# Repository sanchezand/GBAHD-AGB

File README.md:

# GBAHD-AGB Motherboard
This is a replacement AGB motherboard shield for the [gbaHD project](https://github.com/zwenergy/gbaHD).  
- The aim is to remove the CPU and RAM from an original AGB motherboard and place them in this new board.  
- Uses an MCU to connect a classic controller.  
- Has a cartridge slot with a switch to detect DMG/CGB games and switch voltages.
- Has a power switch circuitry to replace Spartan Edge switch.
- Has a better footprint for 3D printed cases

## Issues
- NOT TESTED YET
- Cart sensor switch might need to be changed
- Cart sensor switch footprint might be wrong.
- Clock might need to be rerouted.
- Link port might need to be rerouted
- No 3D printed case (yet)

## Contributing
I am **NOT** an electrical engineer. Take this as a hobby project from a software engineer's attempt at something cool. If you wish to contribute, see something wrong or want to add a feature please make a pull request or leave an issue!

## BOM
Add this later...

## Programming the MCU
**FIRMWARE NOT YET WRITTEN** (following instructions still work)

In order to program the MCU, you need an arduino to use as ISP.  
Use the following image to wire up an arduino to the board to program it.  
**I would also recomend not programming it while seated in the FPGA board.**
  
After wiring the board, follow this tutorial to flash the bootloader and the sketch to the board.  
[ICSP Tutorial](https://www.arduino.cc/en/pmwiki.php?n=Tutorial/ArduinoISP)  
  
The Arduino code requires the [NintendoExtensionCtrl](https://github.com/dmadison/NintendoExtensionCtrl) library.

## Credits
This project would've not existed if it werent for people with real electrical engineering knowledge!
- ARCADETV - (Their AGB schematics seem to have dissapeared)
- Derek F - [GBA-2 Go](https://hackaday.io/project/169998-gba-2-go)
- Zwenergy - [GBAHD Creator](https://github.com/zwenergy/gbaHD)
- dmadison - [Nintendo Controller Libraries](https://github.com/dmadison/NintendoExtensionCtrl)

## Images

## LICENSE
This documentation describes Open Hardware and is licensed under the CERN OHL v. 1.2.
You may redistribute and modify this documentation under the terms of the CERN OHL v.1.2. (http://ohwr.org/cernohl). This documentation is distributed WITHOUT ANY EXPRESS OR IMPLIED WARRANTY, INCLUDING OF MERCHANTABILITY, SATISFACTORY QUALITY AND FITNESS FOR A PARTICULAR PURPOSE. Please see the CERN OHL v.1.2 for applicable conditions.

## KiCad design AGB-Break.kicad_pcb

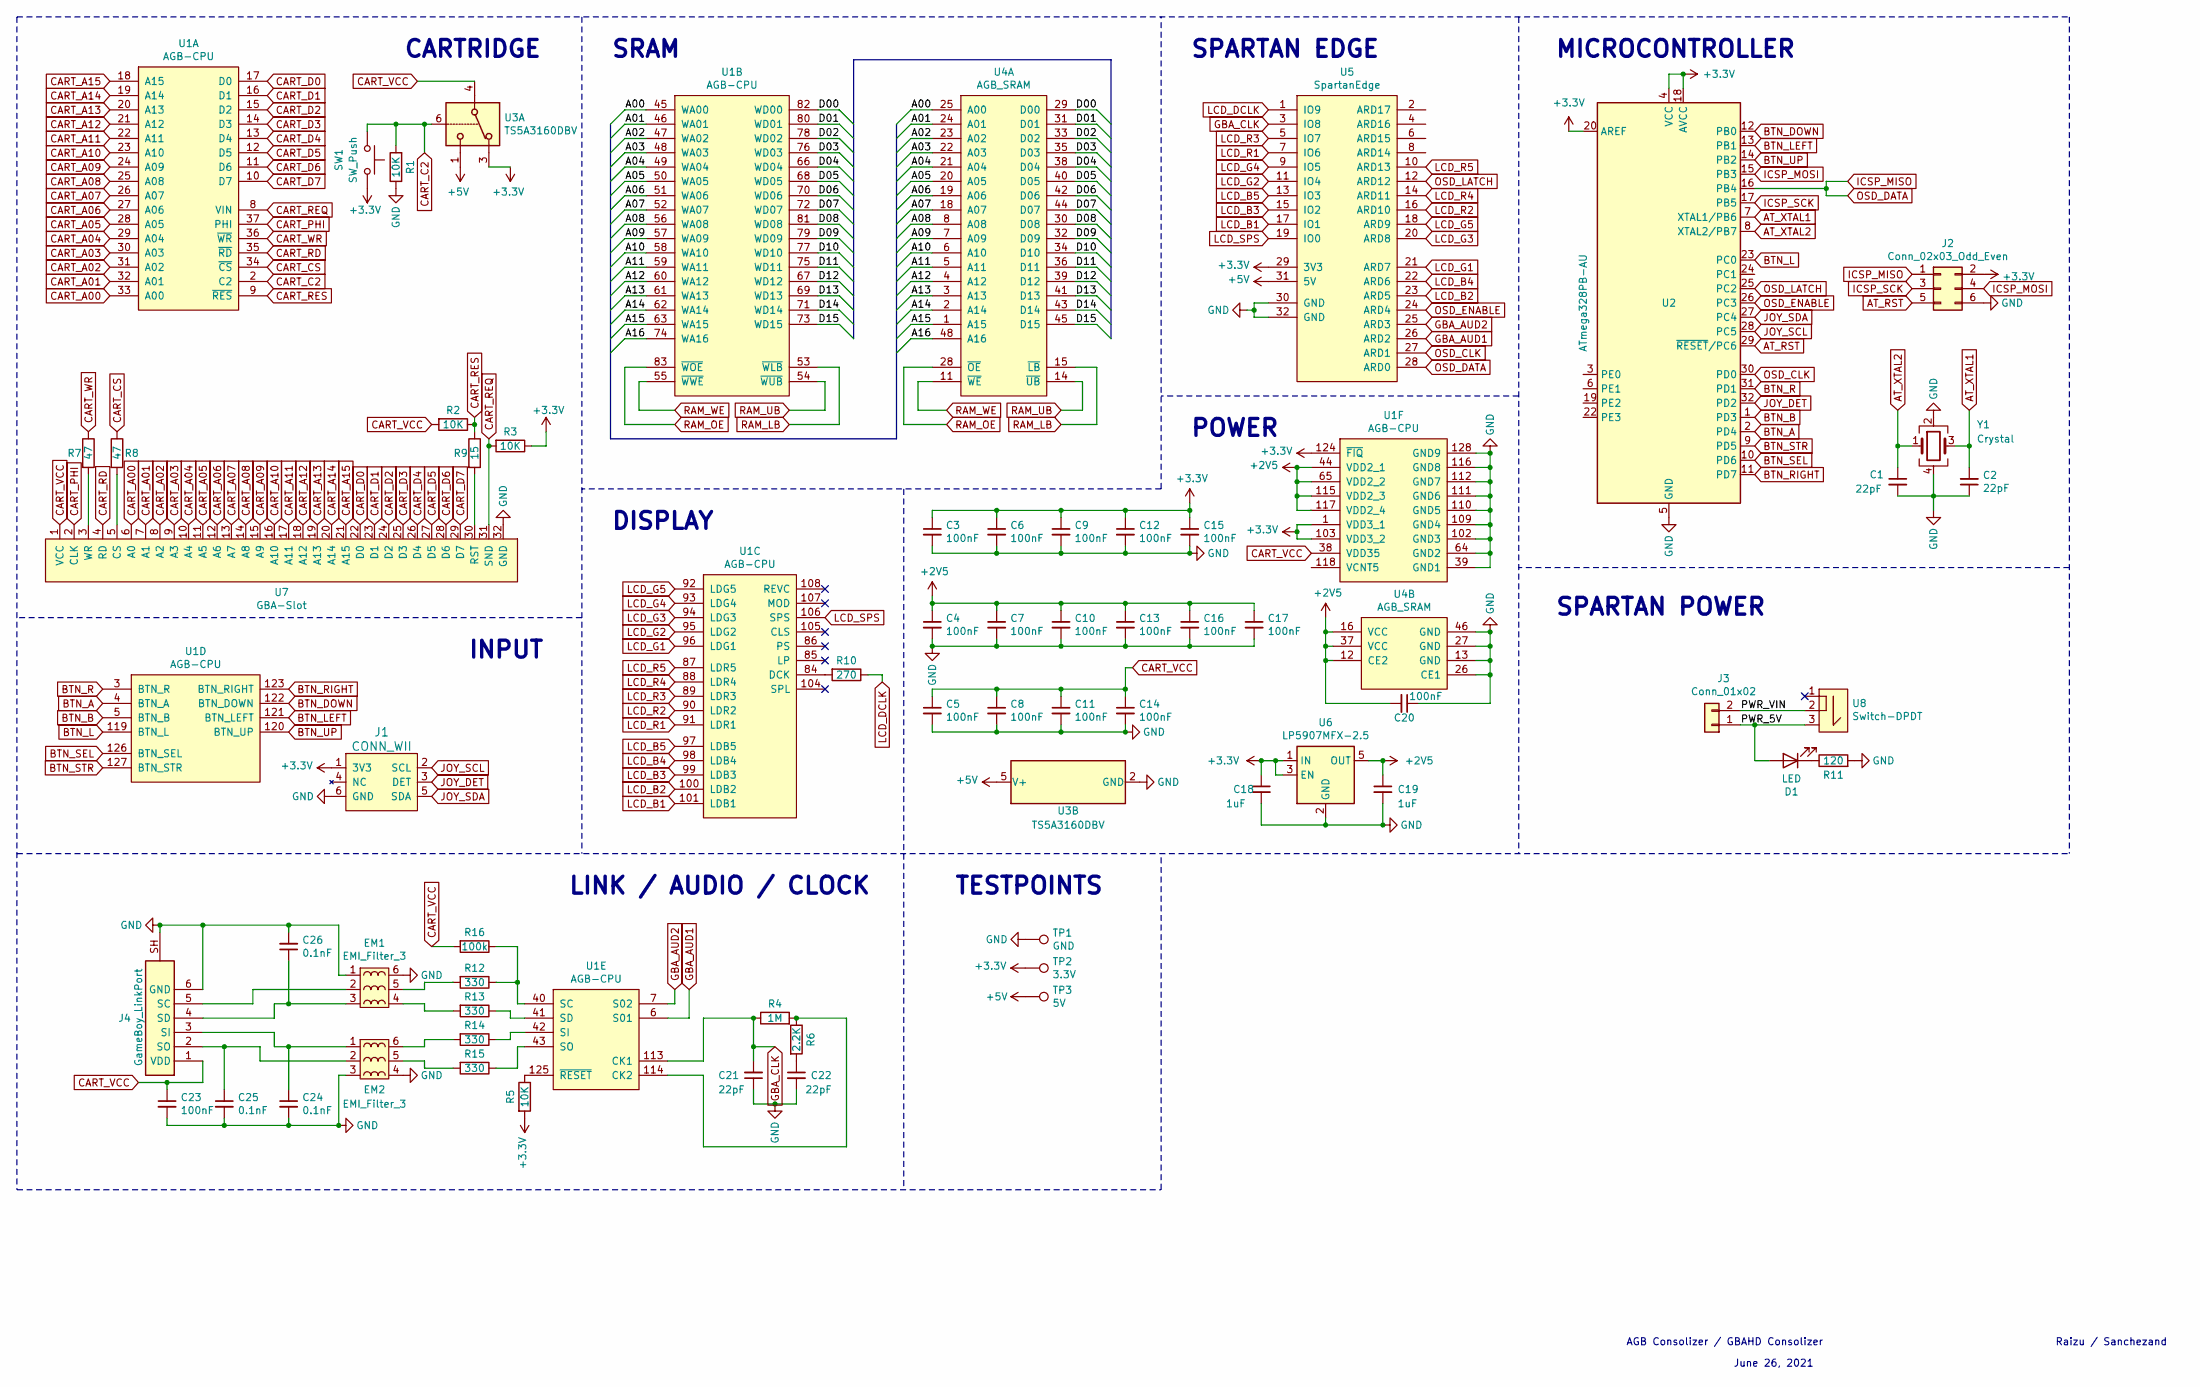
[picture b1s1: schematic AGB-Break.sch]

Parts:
C1, C2, C21, C22: 22pF; C_0805_2012Metric_Pad1.18x1.45mm_HandSolder
C3, C4, C5, C6, C7, C8, C9, C10, C11, C12, C13, C14, C15, C16, C17, C20, C23: 100nF; C_0805_2012Metric_Pad1.18x1.45mm_HandSolder
C18, C19: 1uF; C_0805_2012Metric_Pad1.18x1.45mm_HandSolder
C24, C25, C26: 0.1nF; C_0805_2012Metric_Pad1.18x1.45mm_HandSolder
D1: LED; LED_D5.0mm_FlatTop
EM1, EM2: EMI_Filter_3; Inductor-1008-3P
J1: CONN_WII
J2: Conn_02x03_Odd_Even; PinHeader_2x03_P2.54mm_Vertical
J3: Conn_01x02; PinSocket_1x02_P2.54mm_Vertical
J4: GameBoy_LinkPort; GameBoy_LinkPort_MGB_Horizontal
R1, R2, R3, R5: 10K; R_0805_2012Metric_Pad1.20x1.40mm_HandSolder
R4: 1M; R_0805_2012Metric_Pad1.20x1.40mm_HandSolder
R6: 2.2K; R_0805_2012Metric_Pad1.20x1.40mm_HandSolder
R7, R8: 47; R_0805_2012Metric_Pad1.20x1.40mm_HandSolder
R9: 15; R_0805_2012Metric_Pad1.20x1.40mm_HandSolder
R10: 270; R_0805_2012Metric_Pad1.20x1.40mm_HandSolder
R11: 120; R_0805_2012Metric_Pad1.20x1.40mm_HandSolder
R12, R13, R14, R15: 330; R_0805_2012Metric_Pad1.20x1.40mm_HandSolder
R16: 100k; R_0805_2012Metric_Pad1.20x1.40mm_HandSolder
SW1: SW_Push; Switch_K5-1617SA-01
TP1: GND; SOLDER_PAD
TP2: 3.3V; SOLDER_PAD
TP3: 5V; SOLDER_PAD
U1: AGB-CPU
U2: ATmega328PB-AU; TQFP-32_7x7mm_P0.8mm
U3: TS5A3160DBV; SOT-23-6
U4: AGB_SRAM
U5: SpartanEdge; SpartanEdge_Shield
U6: LP5907MFX-2.5; SOT-23-5
U7: GBA-Slot; GBA_CONNECTOR
U8: Switch-DPDT; XKB_XKB5858-Z-C
Y1: Crystal; Crystal_SMD_3225-4Pin_3.2x2.5mm

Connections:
+2V5: C4.1, C7.1, C10.1, C13.1, C16.1, C17.1, C19.1, C20.2, U1.44 (VDD2_1), U1.65 (VDD2_2), U1.115 (VDD2_3), U1.117 (VDD2_4), U4.12 (CE2), U4.16 (VCC), U4.37 (VCC), U6.5 (OUT)
+3V3: C3.1, C6.1, C9.1, C12.1, C15.1, C18.1, J1.1 (3V3), J2.2, R3.1, R5.2, SW1.2, TP2.1, U1.1 (VDD3_1), U1.103 (VDD3_2), U1.124 (~FIQ), U2.4 (VCC), U2.18 (AVCC), U2.20 (AREF), U3.3, U5.29 (3V3), U6.1 (IN), U6.3 (EN)
+5V: TP3.1, U3.1, U3.5 (V+), U5.31 (5V)
/A00: U1.45 (WA00), U4.25 (A00)
/A01: U1.46 (WA01), U4.24 (A01)
/A02: U1.47 (WA02), U4.23 (A02)
/A03: U1.48 (WA03), U4.22 (A03)
/A04: U1.49 (WA04), U4.21 (A04)
/A05: U1.50 (WA05), U4.20 (A05)
/A06: U1.51 (WA06), U4.19 (A06)
/A07: U1.52 (WA07), U4.18 (A07)
/A08: U1.56 (WA08), U4.8 (A08)
/A09: U1.57 (WA09), U4.7 (A09)
/A10: U1.58 (WA10), U4.6 (A10)
/A11: U1.59 (WA11), U4.5 (A11)
/A12: U1.60 (WA12), U4.4 (A12)
/A13: U1.61 (WA13), U4.3 (A13)
/A14: U1.62 (WA14), U4.2 (A14)
/A15: U1.63 (WA15), U4.1 (A15)
/A16: U1.74 (WA16), U4.48 (A16)
/D00: U1.82 (WD00), U4.29 (D00)
/D01: U1.80 (WD01), U4.31 (D01)
/D02: U1.78 (WD02), U4.33 (D02)
/D03: U1.76 (WD03), U4.35 (D03)
/D04: U1.66 (WD04), U4.38 (D04)
/D05: U1.68 (WD05), U4.40 (D05)
/D06: U1.70 (WD06), U4.42 (D06)
/D07: U1.72 (WD07), U4.44 (D07)
/D08: U1.81 (WD08), U4.30 (D08)
/D09: U1.79 (WD09), U4.32 (D09)
/D10: U1.77 (WD10), U4.34 (D10)
/D11: U1.75 (WD11), U4.36 (D11)
/D12: U1.67 (WD12), U4.39 (D12)
/D13: U1.69 (WD13), U4.41 (D13)
/D14: U1.71 (WD14), U4.43 (D14)
/D15: U1.73 (WD15), U4.45 (D15)
/PWR_5V: D1.2 (A), J3.1, U8.3
/PWR_VIN: J3.2, U8.2
AT_RST: J2.5, U2.29 (~RESET~/PC6)
AT_XTAL1: C2.2, U2.7 (XTAL1/PB6), Y1.3
AT_XTAL2: C1.1, U2.8 (XTAL2/PB7), Y1.1
BTN_A: U1.4 (BTN_A), U2.2 (PD4)
BTN_B: U1.5 (BTN_B), U2.1 (PD3)
BTN_DOWN: U1.122 (BTN_DOWN), U2.12 (PB0)
BTN_L: U1.119 (BTN_L), U2.23 (PC0)
BTN_LEFT: U1.121 (BTN_LEFT), U2.13 (PB1)
BTN_R: U1.3 (BTN_R), U2.31 (PD1)
BTN_RIGHT: U1.123 (BTN_RIGHT), U2.11 (PD7)
BTN_SEL: U1.126 (BTN_SEL), U2.10 (PD6)
BTN_STR: U1.127 (BTN_STR), U2.9 (PD5)
BTN_UP: U1.120 (BTN_UP), U2.14 (PB2)
CART_A00: U1.33 (A00), U7.6 (A0)
CART_A01: U1.32 (A01), U7.7 (A1)
CART_A02: U1.31 (A02), U7.8 (A2)
CART_A03: U1.30 (A03), U7.9 (A3)
CART_A04: U1.29 (A04), U7.10 (A4)
CART_A05: U1.28 (A05), U7.11 (A5)
CART_A06: U1.27 (A06), U7.12 (A6)
CART_A07: U1.26 (A07), U7.13 (A7)
CART_A08: U1.25 (A08), U7.14 (A8)
CART_A09: U1.24 (A09), U7.15 (A9)
CART_A10: U1.23 (A10), U7.16 (A10)
CART_A11: U1.22 (A11), U7.17 (A11)
CART_A12: U1.21 (A12), U7.18 (A12)
CART_A13: U1.20 (A13), U7.19 (A13)
CART_A14: U1.19 (A14), U7.20 (A14)
CART_A15: U1.18 (A15), U7.21 (A15)
CART_C2: R1.2, SW1.1, U1.2 (C2), U3.6
CART_CS: R8.1, U1.34 (~CS)
CART_D0: U1.17 (D0), U7.22 (D0)
CART_D1: U1.16 (D1), U7.23 (D1)
CART_D2: U1.15 (D2), U7.24 (D2)
CART_D3: U1.14 (D3), U7.25 (D3)
CART_D4: U1.13 (D4), U7.26 (D4)
CART_D5: U1.12 (D5), U7.27 (D5)
CART_D6: U1.11 (D6), U7.28 (D6)
CART_D7: U1.10 (D7), U7.29 (D7)
CART_PHI: U1.37 (PHI), U7.2 (CLK~)
CART_RD: U1.35 (~RD), U7.4 (RD)
CART_REQ: R3.2, U1.8 (VIN), U7.31 (SND)
CART_RES: R2.1, R9.1, U1.9 (~RES)
CART_VCC: C5.1, C8.1, C11.1, C14.1, C23.1, J4.1 (VDD), R2.2, R16.2, U1.38 (VDD35), U3.4, U7.1 (VCC)
CART_WR: R7.1, U1.36 (~WR)
GBA_AUD1: U1.6 (S01), U5.26 (ARD2)
GBA_AUD2: U1.7 (S02), U5.25 (ARD3)
GBA_CLK: C21.2, R4.1, U1.113 (CK1), U5.3 (IO8)
GND: C1.2, C2.1, C3.2, C4.2, C5.2, C6.2, C7.2, C8.2, C9.2, C10.2, C11.2, C12.2, C13.2, C14.2, C15.2, C16.2, C17.2, C18.2, C19.2, C20.1, C21.1, C22.2, C23.2, C24.2, C25.2, C26.2, EM1.1, EM1.6, EM2.3, EM2.4, J1.6 (GND), J2.6, J4.6 (GND), J4.SH, R1.1, R11.2, TP1.1, U1.39 (GND1), U1.64 (GND2), U1.102 (GND3), U1.109 (GND4), U1.110 (GND5), U1.111 (GND6), U1.112 (GND7), U1.116 (GND8), U1.128 (GND9), U2.5 (GND), U2.21 (GND), U3.2 (GND), U4.13 (GND), U4.26 (CE1), U4.27 (GND), U4.46 (GND), U5.30 (GND), U5.32 (GND), U6.2 (GND), U7.32 (GND), Y1.2, Y1.4
ICSP_MISO: J2.1, U2.16 (PB4), U5.28 (ARD0)
ICSP_MOSI: J2.4, U2.15 (PB3)
ICSP_SCK: J2.3, U2.17 (PB5)
JOY_DET: J1.3 (DET), U2.32 (PD2)
JOY_SCL: J1.2 (SCL), U2.28 (PC5)
JOY_SDA: J1.5 (SDA), U2.27 (PC4)
LCD_B1: U1.101 (LDB1), U5.17 (IO1)
LCD_B2: U1.100 (LDB2), U5.23 (ARD5)
LCD_B3: U1.99 (LDB3), U5.15 (IO2)
LCD_B4: U1.98 (LDB4), U5.22 (ARD6)
LCD_B5: U1.97 (LDB5), U5.13 (IO3)
LCD_DCLK: R10.1, U5.1 (IO9)
LCD_G1: U1.96 (LDG1), U5.21 (ARD7)
LCD_G2: U1.95 (LDG2), U5.11 (IO4)
LCD_G3: U1.94 (LDG3), U5.20 (ARD8)
LCD_G4: U1.93 (LDG4), U5.9 (IO5)
LCD_G5: U1.92 (LDG5), U5.18 (ARD9)
LCD_R1: U1.91 (LDR1), U5.7 (IO6)
LCD_R2: U1.90 (LDR2), U5.16 (ARD10)
LCD_R3: U1.89 (LDR3), U5.5 (IO7)
LCD_R4: U1.88 (LDR4), U5.14 (ARD11)
LCD_R5: U1.87 (LDR5), U5.10 (ARD13)
LCD_SPS: U1.106 (SPS), U5.19 (IO0)
unnamed: C22.1, R6.2
unnamed: C24.1, EM2.1, J4.3 (SI)
unnamed: C25.1, EM2.2, J4.2 (SO)
unnamed: C26.1, EM1.3, J4.4 (SD)
unnamed: D1.1 (K), R11.1
unnamed: EM1.2, J4.5 (SC)
unnamed: EM1.4, R13.2
unnamed: EM1.5, R12.2
unnamed: EM2.5, R15.2
unnamed: EM2.6, R14.2
unnamed: R4.2, R6.1, U1.114 (CK2)
unnamed: R5.1, U1.125 (~RESET)
unnamed: R7.2, U7.3 (WR)
unnamed: R8.2, U7.5 (CS)
unnamed: R9.2, U7.30 (RST)
unnamed: R10.2, U1.84 (DCK)
unnamed: R12.1, R16.1, U1.40 (SC)
unnamed: R13.1, U1.41 (SD)
unnamed: R14.1, U1.42 (SI)
unnamed: R15.1, U1.43 (SO)
OSD_CLK: U2.30 (PD0), U5.27 (ARD1)
OSD_ENABLE: U2.26 (PC3), U5.24 (ARD4)
OSD_LATCH: U2.25 (PC2), U5.12 (ARD12)
RAM_LB: U1.53 (~WLB), U4.15 (~LB)
RAM_OE: U1.83 (~WOE), U4.28 (~OE)
RAM_UB: U1.54 (~WUB), U4.14 (~UB)
RAM_WE: U1.55 (~WWE), U4.11 (~WE)

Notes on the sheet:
CARTRIDGE
AGB Consolizer / GBAHD Consolizer
June 26, 2021
Raizu / Sanchezand
SRAM
SPARTAN EDGE
POWER
DISPLAY
INPUT
MICROCONTROLLER
SPARTAN POWER
LINK / AUDIO / CLOCK
TESTPOINTS

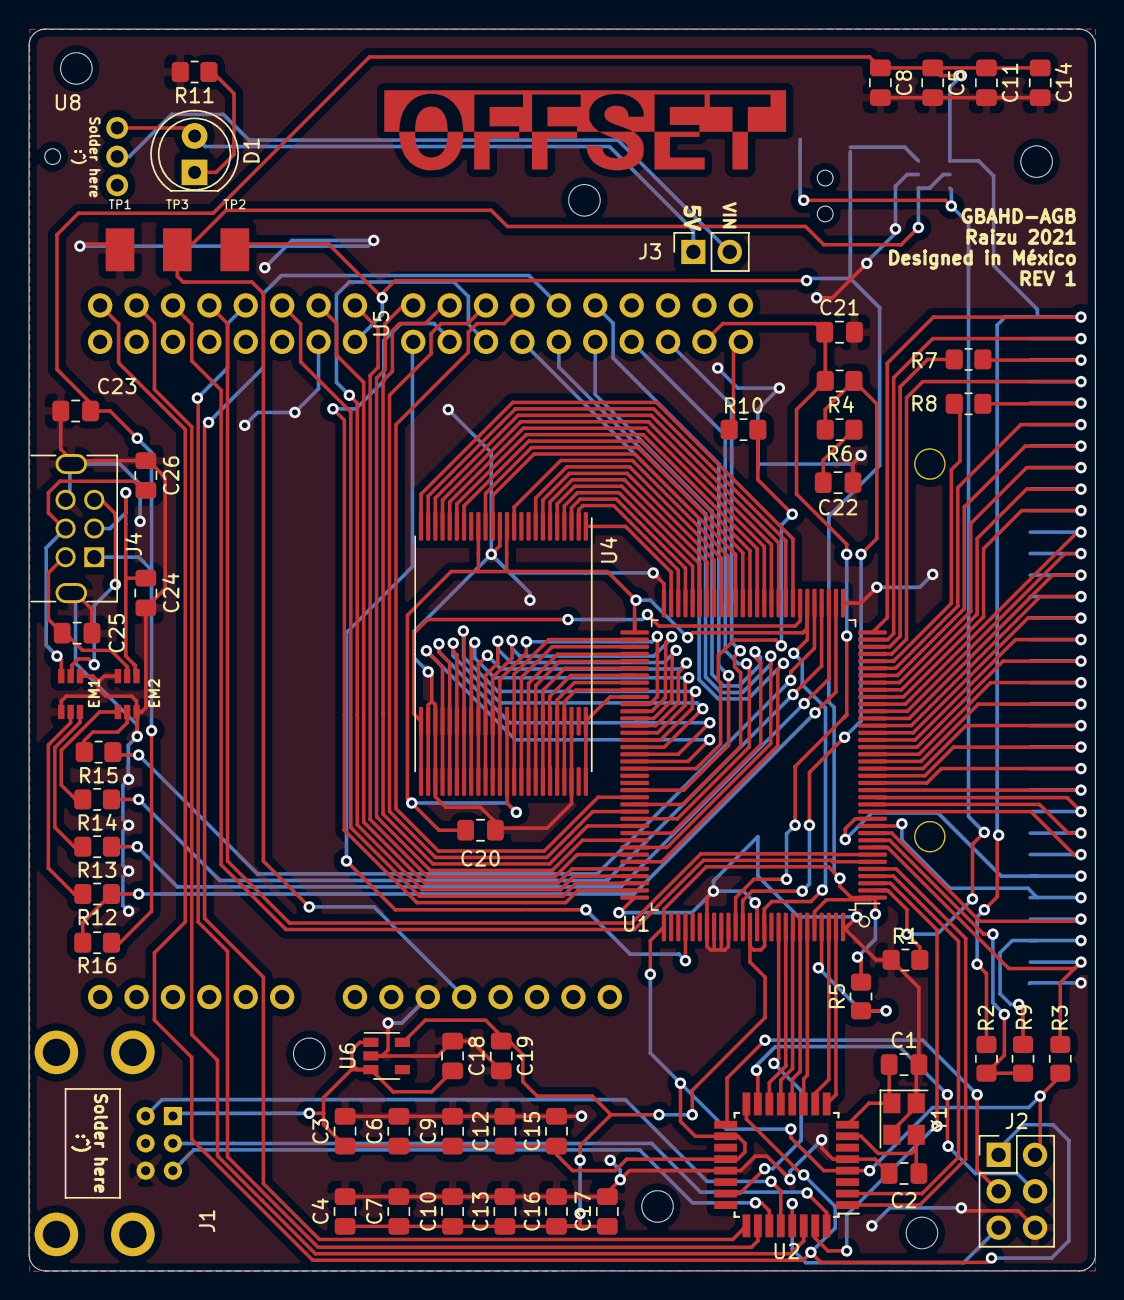
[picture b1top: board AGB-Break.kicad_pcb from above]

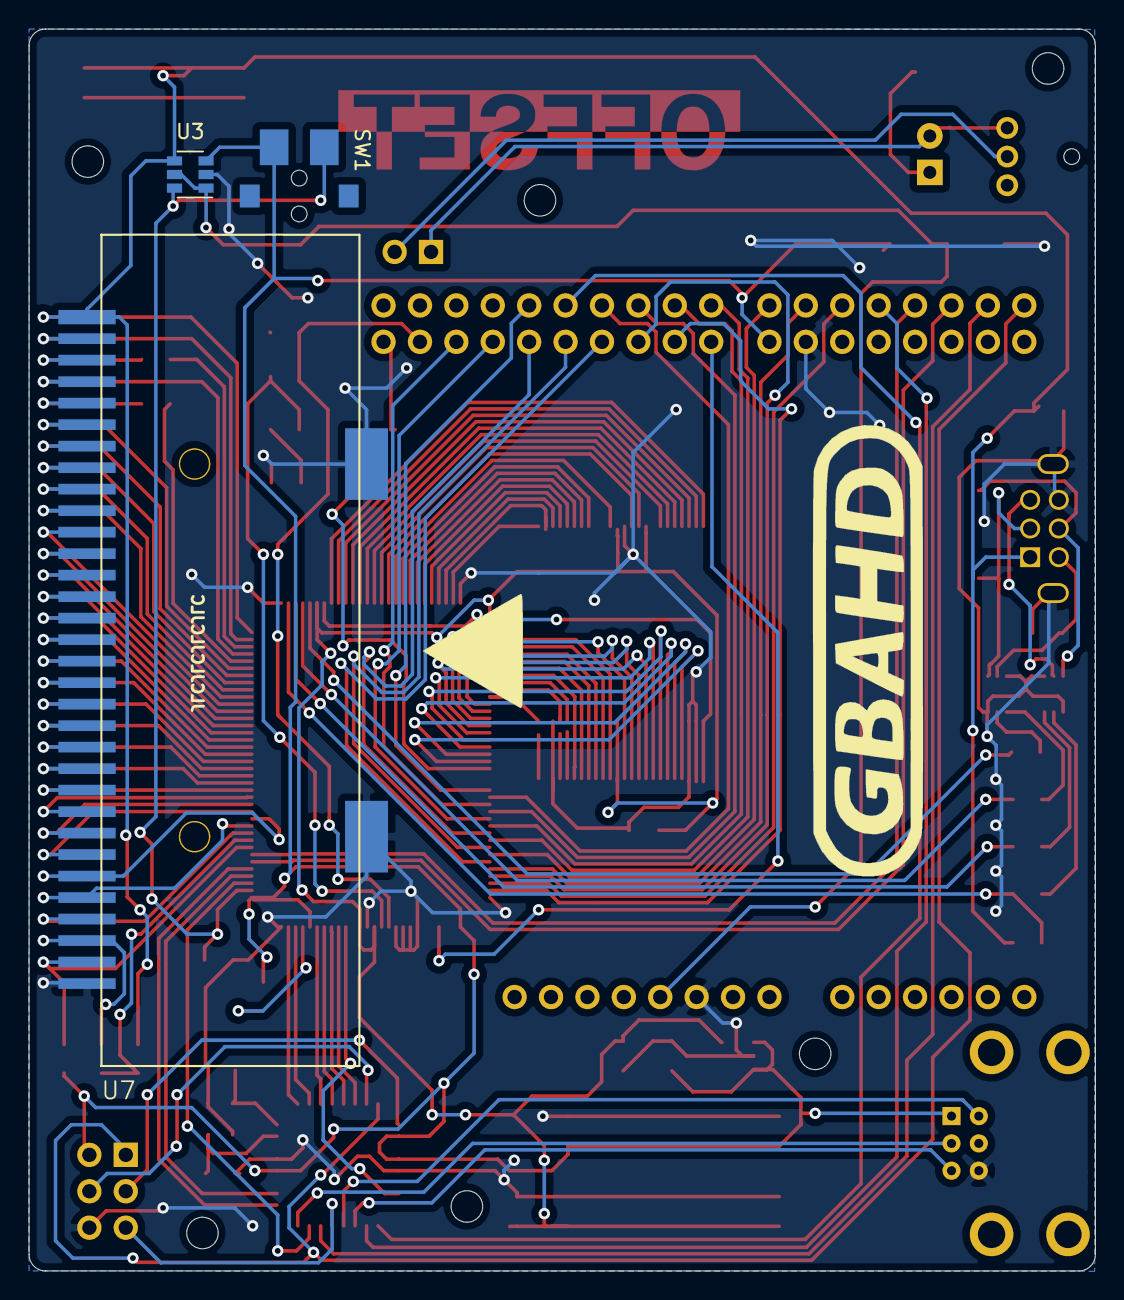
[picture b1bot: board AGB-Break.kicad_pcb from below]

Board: 2 copper layers, 74.4 x 86.7 mm, 62 parts (4 on the bottom side), 137 nets.

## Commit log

2021-06-28 Initial commit, not done yet.
2021-07-01 Finished current routing, still missing power switch.
2021-07-02 Finished PCB v1
2021-07-07 Finished PCB work, but headers are flipped, need to fix this :(
2021-07-08 Finished PCB layout, sent to pcb fab.
2021-08-01 Changed clock wiring
2021-08-01 Added readme/license
2021-08-01 Added PDF schematic
